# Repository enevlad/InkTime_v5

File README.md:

# InkTime v5

A low-power e-paper smartwatch based on the Nordic nRF52840 SoC, featuring Bluetooth LE, haptic feedback, and a 3-button interface.

## Block Diagram

```
                        ┌─────────────────────────────────────────┐
                        │              nRF52840                    │
                        │                                          │
 USB-C ──► BQ25180 ──►  │  SPI ──► E-Paper Display (2.9")         │
           (LiPo        │  I2C ──► BMA423 (IMU)                   │
           Charger)      │  I2C ──► DRV2605 (Haptic)               │
              │          │  I2C ──► MAX17048 (Fuel Gauge)          │
              ▼          │  I2C ──► BQ25180 (Charger)              │
           RT6160 ──────►│  I2C ──► RT6160 (DC/DC)                 │
           (DC/DC        │  GPIO ► SW_UP, SW_ENT, SW_DN (Buttons)  │
           3.3V)         │  SWD ──► TC2030 Debug Connector         │
                        │  ANT ──► 2450AT18B100E (BLE Antenna)    │
                        └─────────────────────────────────────────┘
```

## Bill of Materials

| Reference | Component | Value | Description | JLC Part | Datasheet |
|-----------|-----------|-------|-------------|----------|-----------|
| U1 | nRF52840 | - | BLE SoC, main MCU | - | - |
| U2 | RT6160AWSC | - | DC/DC Buck Converter 3.3V | - | - |
| U3 | MAX17048G+T10 | - | LiPo Fuel Gauge | - | - |
| U4 | BQ25180YBGR | - | LiPo Charger | - | - |
| U5 | DRV2605YZFR | - | Haptic Driver | - | - |
| U6 | BMA423 | - | IMU (Accelerometer) | - | - |
| U7 | SI1308EDL-T1-GE3 | - | P-Channel MOSFET (EPD Power Switch) | - | - |
| D1 | MBR0530 | - | Schottky Diode (DC/DC) | - | -.pdf) |
| D2, D3 | MBR0530 | - | Schottky Diode (EPD Drive) | - | -.pdf) |
| D4 | USBLC6-2SC6Y | - | USB ESD Protection | - | - |
| L1 | 2450AT18B100E | - | 2.4GHz BLE Chip Antenna | - | - |
| L2 | FTC252012SR47MBCA | 4.7µH | Inductor (DC/DC) | - | - |
| J1 | KH-TYPE-C-16P | - | USB-C Connector | - | - |
| J2 | TC2030-IDC | - | SWD Debug Connector | - | - |
| J3 | 503480-2400 | - | E-Paper FPC Connector 24-pin | - | - |
| SW1 | SW_UP | - | Tactile Button | - | - |
| SW2 | SW_ENT | - | Tactile Button | - | - |
| SW3 | SW_DN | - | Tactile Button | - | - |
| BAT1 | AKYGA LP502030 | 3.7V/250mAh | LiPo Battery | - | - |

## Hardware Description

### Power Architecture

The device is powered by a **3.7V LiPo battery (AKYGA LP502030, 250mAh)**. Charging is handled by the **BQ25180** via USB-C (5V VBUS). The BQ25180 communicates with the nRF52840 over **I²C** (PMC_INT alert pin) for charge status monitoring.

The **RT6160 DC/DC buck converter** steps down VBAT to **3.3V** for the nRF52840 and all peripherals. It is also controlled via I²C from the nRF (SW1/SW2 pins for dynamic voltage scaling).

Battery state of charge is monitored by the **MAX17048 fuel gauge** over I²C (ALERT pin connected to nRF GPIO).

The **E-Paper display** has a separate power rail (**EPD_3V3**) switched by a P-channel MOSFET (SI1308EDL) controlled by a GPIO on the nRF52840. This allows the display to be fully powered off between updates to save energy.

### nRF52840 Pin Assignment

| nRF52840 Pin | Net | Peripheral | Interface |
|-------------|-----|-----------|-----------|
| P0.26 / XL1 | EPD_CLK | E-Paper Display | SPI CLK |
| P0.27 / XL2 | EPD_MOSI | E-Paper Display | SPI MOSI |
| P0.01 | EPD_CS | E-Paper Display | SPI CS |
| P0.00 | EPD_DC | E-Paper Display | SPI DC |
| P0.09 | EPD_RST | E-Paper Display | GPIO |
| P0.10 | EPD_BUSY | E-Paper Display | GPIO Input |
| P0.26 | SCL | I²C Bus (BQ25180, RT6160, MAX17048, DRV2605) | I²C SCL |
| P0.25 | SDA | I²C Bus | I²C SDA |
| P0.06 | IMU_INT1 | BMA423 | GPIO Input |
| P0.05 | IMU_INT2 | BMA423 | GPIO Input |
| P0.07 | HAPTIC_EN | DRV2605 | GPIO Enable |
| P0.08 | EPD_PWR_EN | SI1308EDL Gate | GPIO |
| P0.11 | SW_UP | Button Up | GPIO Input |
| P0.12 | SW_ENT | Button Enter | GPIO Input |
| P0.13 | SW_DN | Button Down | GPIO Input |
| P0.18 | RESET | Reset | Active Low |
| SWDIO | SWDIO | TC2030 SWD | Debug |
| SWDCLK | SWDCLK | TC2030 SWD | Debug |
| ANT | ANT | 2450AT18B100E | RF 2.4GHz |

### E-Paper Display

The E-Paper display connects via a **24-pin FPC connector (503480-2400)**. The drive circuit uses a boost converter based on the SI1308 MOSFET and MBR0530 diodes to generate the high voltages required for the EPD gate drivers (PREVGH ~15V, PREVGL ~-15V). Communication is via SPI.

### IMU

The **BMA423** accelerometer connects via I²C and provides step counting, activity detection, and wrist-tilt detection. Two interrupt lines (IMU_INT1, IMU_INT2) allow wake-on-motion functionality to minimize power consumption.

### Haptic Feedback

The **DRV2605** haptic driver connects via I²C and drives an ERM or LRA vibration motor. It is enabled via a dedicated GPIO from the nRF52840 (HAPTIC_EN).

### BLE Antenna

The **2450AT18B100E** chip antenna is placed at the corner of the PCB with a full copper keepout zone on all layers beneath it, as required by the antenna datasheet for optimal RF performance.

### USB & ESD Protection

The **KH-TYPE-C-16P** USB-C connector includes CC1/CC2 pins for USB PD negotiation. The **USBLC6-2SC6Y** TVS diode array provides ESD protection on the D+/D- lines. A 1kΩ resistor limits inrush current on VBUS.

### SWD Debug Interface

Programming and debugging is done via a **TC2030-IDC Tag-Connect** footprint, exposing SWDIO, SWDCLK, RESET, 3V3, and GND. No physical connector is required — the Tag-Connect pogo-pin cable clips directly onto the PCB pads.

## Power Consumption Estimates

| Mode | Current | Notes |
|------|---------|-------|
| BLE Advertising | ~0.5mA avg | 1s interval |
| BLE Connected | ~1.5mA avg | Active connection |
| Deep Sleep | ~3µA | nRF System OFF, RTC wake |
| E-Paper Refresh | ~20mA peak | During display update only |
| Haptic Active | ~50mA peak | Motor running |
| **Estimated avg (watch mode)** | **~0.3mA** | 1 EPD refresh/min, BLE adv |

Estimated battery life with 250mAh: **~30 days** in watch mode.

## PCB

- **Layers:** 3 (Top signal, GND plane, Bottom signal)
- **Dimensions:** ~54 × 40mm
- **Fabrication:** JLCPCB 4-layer standard
- **Min trace width:** 0.15mm
- **Min clearance:** 0.15mm

## License

Apache License 2.0 — see [LICENSE](LICENSE)

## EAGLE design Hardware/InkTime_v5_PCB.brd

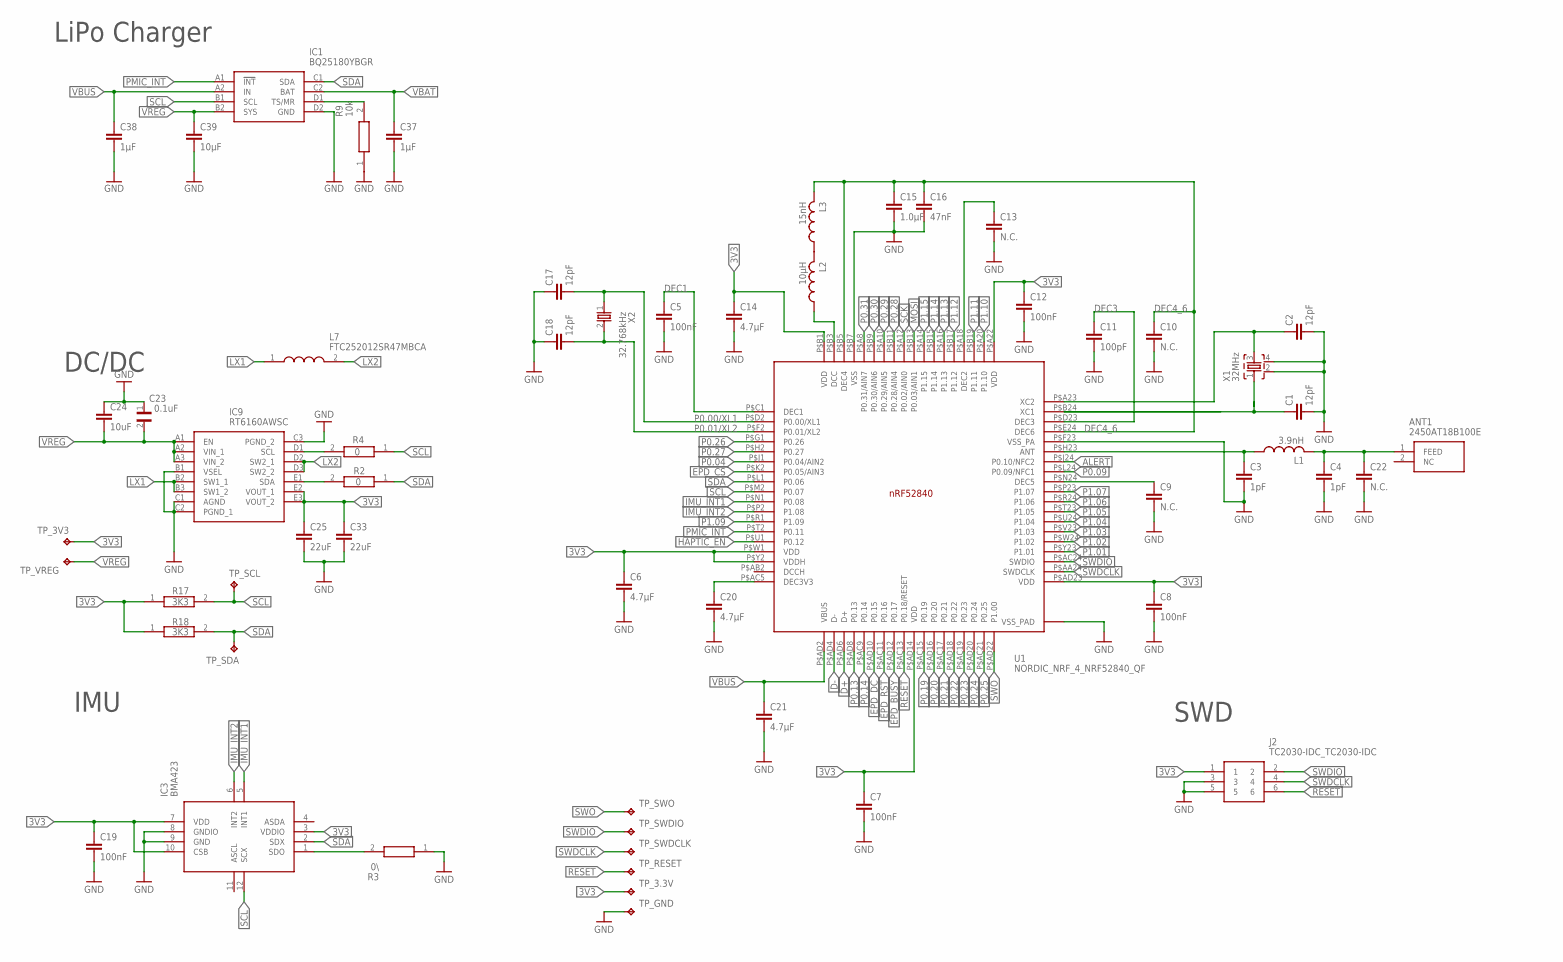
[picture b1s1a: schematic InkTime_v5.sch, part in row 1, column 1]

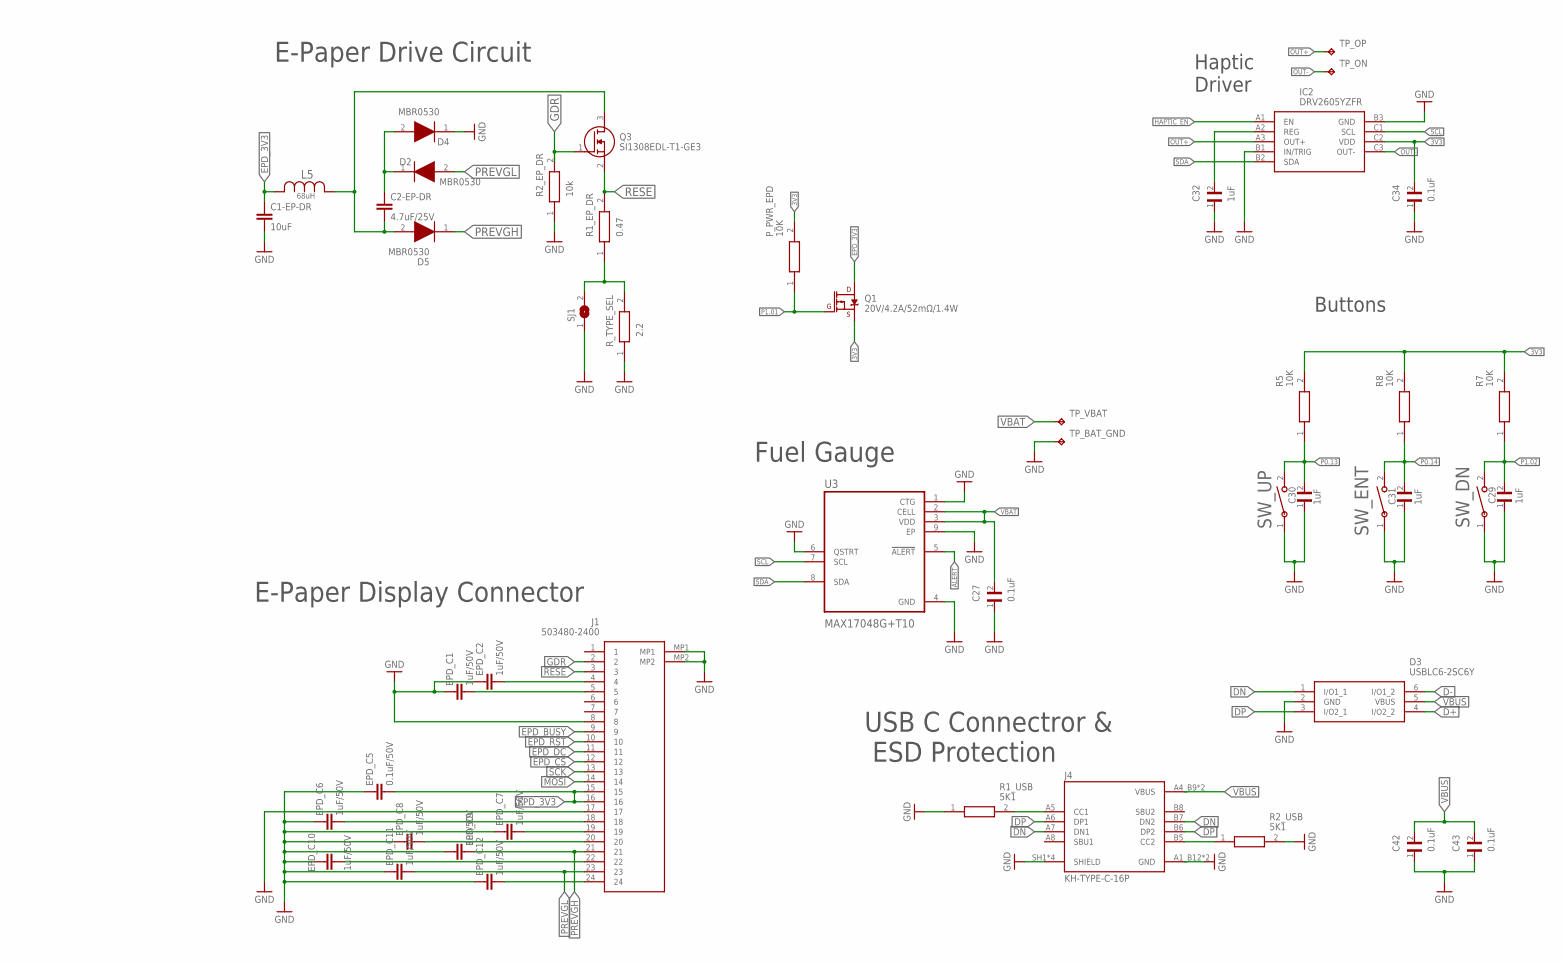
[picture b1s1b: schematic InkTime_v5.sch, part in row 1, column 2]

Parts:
ANT1: 2450AT18B100E; 2450AT18B100E_ANTC3216X140N
C1, C2, C17, C18: 12pF; NORDIC_NRF_3_RESC0201_L
C1-EP-DR, C24: 10uF; PERFECT_0402_0402
C2-EP-DR: 4.7uF/25V; PERFECT_0402_0402
C3, C4: 1pF; NORDIC_NRF_3_RESC0201_L
C5, C7, C8, C12, C19: 100nF; NORDIC_NRF_3_RESC0201_L
C6, C14, C20, C21: 4.7µF; PERFECT_0402_0402
C9, C10, C13, C22: N.C.; NORDIC_NRF_3_RESC0201_L
C11: 100pF; NORDIC_NRF_3_RESC0201_L
C15: 1.0µF; PERFECT_0402_0402
C16: 47nF; NORDIC_NRF_3_RESC0201_L
C23, C27, C34, C42, C43: 0.1uF; GRM011R60J152KE01L_2_CAPC0201X13N
C25, C33: 22uF; PERFECT_0402_0402
C29, C30, C31, C32: 1uF; GRM011R60J152KE01L_2_CAPC0201X13N
C37, C38: 1µF; PERFECT_0402_0402
C39: 10µF; PERFECT_0402_0402
D2, D4, D5: MBR0530; ESP32_C6_LIBRARY_5_SOD3716X135N
D3: USBLC6-2SC6Y; ESP32_C6_LIBRARY_3_SOT95P280X145-6N
EPD_C1, EPD_C2, EPD_C6, EPD_C7, EPD_C8, EPD_C9, EPD_C10, EPD_C11, EPD_C12: 1uF/50V; PERFECT_0402_0402
EPD_C5: 0.1uF/50V; NORDIC_NRF_3_RESC0201_L
IC1: BQ25180YBGR; BQ25180YBGR_BGA8C40P2X4_100X155X50
IC2: DRV2605YZFR; DRV2605YZFR_BGA9C50P3X3_144X144X62
IC3: BMA423; BMA423_BMA423
IC9: RT6160AWSC; RT6160AWSC_BGA15C40P3X5_140X230X60
J1: 503480-2400; 503480-2400_5034802400
J2: TC2030-IDC_TC2030-IDC; TC2030-IDC_TC2030IDC
J4: KH-TYPE-C-16P; KH-TYPE-C-16P_KINGHELM_KH-TYPE-C-16P
L1: 3.9nH; NORDIC_NRF_2_RESC0402_L
L2: 10µH; NORDIC_NRF_2_RESC0402_L
L3: 15nH; NORDIC_NRF_2_RESC0402_L
L5: 68uH; ESP32_C6_LIBRARY_2_IND_4828-WE-TPC_WRE
L7: FTC252012SR47MBCA; MLP2016SR47MT0S1_INDC2016X100N
P_PWR_EPD: 10K; ERA-1AEB3401C_0201
Q1: 20V/4.2A/52mΩ/1.4W; ESP32_C6_LIBRARY_4_ESP32_C6_LIBRARY_4_ESP32_C6_LIBRARY_4_ES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
Q3: SI1308EDL-T1-GE3; ESP32_C6_LIBRARY_6_SOT65P210X110-3N
R1_EP_DR: 0.47; CPF0201D7K68C1_0201
R1_USB, R2_USB: 5K1; ERA-1AEB3401C_0201
R2: 0; ERA-1AEB3401C_0201
R2_EP_DR, R9: 10k; CPF0201D7K68C1_0201
R3: 0\; CPF0201D7K68C1_0201
R4: 0; CPF0201D7K68C1_0201
R5, R7, R8: 10K; ERA-1AEB3401C_0201
R17, R18: 3K3; ERA-1AEB3401C_0201
R_TYPE_SEL: 2.2; CPF0201D7K68C1_0201
SJ1: ESP32_C6_LIBRARY_7_JUMPER_SJ
SW_DN: 2025-10-22_07-23-44_LIBRARY_EVP-AKE31ASW_EVP-AKE3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; 2025-10-22_07-23-44_LIBRARY_SW_EVP-AKE31A_PAN
SW_ENT: 2025-10-22_07-23-44_LIBRARY_EVP-AKE31ASW_EVP-AKE3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; 2025-10-22_07-23-44_LIBRARY_SW_EVP-AKE31A_PAN
SW_UP: 2025-10-22_07-23-44_LIBRARY_EVP-AKE31ASW_EVP-AKE3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; 2025-10-22_07-23-44_LIBRARY_SW_EVP-AKE31A_PAN
TP_3.3V, TP_3V3: HECTOR_WATCH_1_TPTP20R; HECTOR_WATCH_1_TP20R
TP_BAT_GND: HECTOR_WATCH_1_TPTP20R; HECTOR_WATCH_1_TP20R
TP_GND: HECTOR_WATCH_1_TPTP20R; HECTOR_WATCH_1_TP20R
TP_ON: HECTOR_WATCH_1_TPTP20R; HECTOR_WATCH_1_TP20R
TP_OP: HECTOR_WATCH_1_TPTP20R; HECTOR_WATCH_1_TP20R
TP_RESET: HECTOR_WATCH_1_TPTP20R; HECTOR_WATCH_1_TP20R
TP_SCL: HECTOR_WATCH_1_TPTP20R; HECTOR_WATCH_1_TP20R
TP_SDA: HECTOR_WATCH_1_TPTP20R; HECTOR_WATCH_1_TP20R
TP_SWDCLK: HECTOR_WATCH_1_TPTP20R; HECTOR_WATCH_1_TP20R
TP_SWDIO: HECTOR_WATCH_1_TPTP20R; HECTOR_WATCH_1_TP20R
TP_SWO: HECTOR_WATCH_1_TPTP20R; HECTOR_WATCH_1_TP20R
TP_VBAT: HECTOR_WATCH_1_TPTP20R; HECTOR_WATCH_1_TP20R
TP_VREG: HECTOR_WATCH_1_TPTP20R; HECTOR_WATCH_1_TP20R
U1: NORDIC_NRF_4_NRF52840_QF; NORDIC_NRF_4_AQFN50P700X700X85_HS-74N
U3: MAX17048G+T10; ESP32_C6_LIBRARY_SON50P200X200X80-9N
X1: 32MHz; NORDIC_NRF_BT-XTAL_2016_N
X2: 32.768kHz; NORDIC_NRF_1_XTAL_3215_N

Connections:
3V3: C6.1, C7.1, C8.1, C12.1, C14.1, C19.1, C25.1, C33.1, C34.2, IC2.C2 (VDD), IC3.3 (VDDIO), IC3.7 (VDD), IC3.10 (CSB), IC9.E2 (VOUT_1), IC9.E3 (VOUT_2), J2.1, P_PWR_EPD.2, Q1.2 (S), R5.2, R7.2, R8.2, R17.1, R18.1, TP_3.3V.TP, TP_3V3.TP, U1.P$A22 (VDD), U1.P$AD14 (VDD), U1.P$AD23 (VDD), U1.P$B1 (VDD), U1.P$W1 (VDD), U1.P$Y2 (VDDH)
ALERT: U1.P$J24 (P0.10/NFC2), U3.5 (!ALERT)
D+: D3.4 (I/O2_2), U1.P$AD6 (D+)
D-: D3.6 (I/O1_2), U1.P$AD4 (D-)
DEC1: C5.1, U1.P$C1 (DEC1)
DEC3: C11.1, U1.P$D23 (DEC3)
DEC4_6: C10.1, C15.1, C16.1, L3.2, U1.P$B5 (DEC4), U1.P$E24 (DEC6)
DN: D3.1 (I/O1_1), J4.A7 (DN1), J4.B7 (DN2)
DP: D3.3 (I/O2_1), J4.A6 (DP1), J4.B6 (DP2)
EPD_3V3: C1-EP-DR.1, EPD_C5.2, J1.15, J1.16, L5.2, Q1.3 (D)
EPD_BUSY: J1.9, U1.P$AD12 (P0.17)
EPD_CS: J1.12, U1.P$K2 (P0.05/AIN3)
EPD_DC: J1.11, U1.P$AD10 (P0.15)
EPD_RST: J1.10, U1.P$AC11 (P0.16)
GDR: J1.2, Q3.1 (G), R2_EP_DR.2
GND: C1.2, C1-EP-DR.2, C2.2, C3.2, C4.2, C5.2, C6.2, C7.2, C8.2, C9.2, C10.2, C11.2, C12.2, C13.2, C14.2, C15.2, C16.2, C17.1, C18.1, C19.2, C20.2, C21.2, C22.2, C23.1, C24.1, C25.2, C27.1, C29.1, C30.1, C31.1, C32.1, C33.2, C34.1, C37.2, C38.2, C39.2, C42.1, C43.1, D3.2 (GND), D4.1 (K), EPD_C1.1, EPD_C2.1, EPD_C5.1, EPD_C6.1, EPD_C7.1, EPD_C8.1, EPD_C9.1, EPD_C10.1, EPD_C11.1, EPD_C12.1, IC1.D2 (GND), IC2.B1 (IN/TRIG), IC2.B3 (GND), IC3.8 (GNDIO), IC3.9 (GND), IC9.B1 (VSEL), IC9.C1 (AGND), IC9.C2 (PGND_1), IC9.C3 (PGND_2), J1.8, J1.17, J1.MP1, J1.MP2, J2.3, J2.5, J4.A1_B12 (GND), J4.A12_B1 (GND), J4.SH1 (SHIELD), J4.SH2 (SHIELD), J4.SH3 (SHIELD), J4.SH4 (SHIELD), R1_USB.1, R2_EP_DR.1, R2_USB.2, R3.1, R9.1, SJ1.1, SW_DN.1, SW_ENT.1, SW_UP.1, TP_BAT_GND.TP, TP_GND.TP, U1.P$74 (VSS_PAD), U1.P$75 (VSS_PAD), U1.P$76 (VSS_PAD), U1.P$77 (VSS_PAD), U1.P$78 (VSS_PAD), U1.P$79 (VSS_PAD), U1.P$80 (VSS_PAD), U1.P$81 (VSS_PAD), U1.P$82 (VSS_PAD), U1.P$83 (VSS_PAD), U1.P$84 (VSS_PAD), U1.P$85 (VSS_PAD), U1.P$86 (VSS_PAD), U1.P$87 (VSS_PAD), U1.P$88 (VSS_PAD), U1.P$89 (VSS_PAD), U1.P$90 (VSS_PAD), U1.P$B7 (VSS), U1.P$F23 (VSS_PA), U3.1 (CTG), U3.4 (GND), U3.6 (QSTRT), U3.9 (EP), X1.2, X1.4
HAPTIC_EN: IC2.A1 (EN), U1.P$U1 (P0.12)
IMU_INT1: IC3.5 (INT1), U1.P$N1 (P0.08)
IMU_INT2: IC3.6 (INT2), U1.P$P2 (P1.08)
LX1: IC9.B2 (SW1_1), IC9.B3 (SW1_2), L7.1
LX2: IC9.D2 (SW2_1), IC9.D3 (SW2_2), L7.2
MOSI: J1.14, U1.P$B13 (P0.03/AIN1)
unnamed: IC1.D1 (TS/MR), R9.2
unnamed: IC9.D1 (SCL), R4.2
unnamed: IC9.E1 (SDA), R2.2
unnamed: IC3.1 (SDO), R3.2
unnamed: C20.1, U1.P$AC5 (DEC3V3)
unnamed: L2.1, U1.P$B3 (DCC)
unnamed: L2.2, L3.1
unnamed: C2.1, U1.P$A23 (XC2), X1.3
unnamed: C13.1, U1.P$A18 (DEC2)
unnamed: C1.1, U1.P$B24 (XC1)
unnamed: ANT1.1 (FEED), C4.1, C22.1, L1.2
unnamed: C3.1, L1.1, U1.P$H23 (ANT)
unnamed: C9.1, U1.P$N24 (DEC5)
unnamed: C32.2, IC2.A2 (REG)
unnamed: C2-EP-DR.2, D5.2 (A), L5.1, Q3.3 (D)
unnamed: C2-EP-DR.1, D2.1 (K), D4.2 (A)
unnamed: R1_EP_DR.1, R_TYPE_SEL.2, SJ1.2
unnamed: EPD_C2.2, J1.4
unnamed: EPD_C1.2, J1.5
unnamed: EPD_C6.2, J1.18
unnamed: EPD_C7.2, J1.19
unnamed: EPD_C8.2, J1.20
unnamed: J4.A5 (CC1), R1_USB.2
unnamed: EPD_C10.2, J1.22
unnamed: J4.B5 (CC2), R2_USB.1
unnamed: EPD_C12.2, J1.24
OUT+: IC2.A3 (OUT+), TP_OP.TP
OUT-: IC2.C3 (OUT-), TP_ON.TP
P0.00/XL1: C17.2, U1.P$D2 (P0.00/XL1), X2.1
P0.01/XL2: C18.2, U1.P$F2 (P0.01/XL2), X2.2
P0.04: U1.P$J1 (P0.04/AIN2)
P0.09: U1.P$L24 (P0.09/NFC1)
P0.13: C30.2, R5.1, SW_UP.2, U1.P$AD8 (P0.13)
P0.14: C31.2, R8.1, SW_ENT.2, U1.P$AC9 (P0.14)
P0.19: U1.P$AC15 (P0.19)
P0.20: U1.P$AD16 (P0.20)
P0.21: U1.P$AC17 (P0.21)
P0.22: U1.P$AD18 (P0.22)
P0.23: U1.P$AC19 (P0.23)
P0.24: U1.P$AD20 (P0.24)
P0.25: U1.P$AC21 (P0.25)
P0.26: U1.P$G1 (P0.26)
P0.27: U1.P$H2 (P0.27)
P0.28: U1.P$B11 (P0.28/AIN4)
P0.29: U1.P$A10 (P0.29/AIN5)
P0.30: U1.P$B9 (P0.30/AIN6)
P0.31: U1.P$A8 (P0.31/AIN7)
P1.01: P_PWR_EPD.1, Q1.1 (G), U1.P$Y23 (P1.01)
P1.02: C29.2, R7.1, SW_DN.2, U1.P$W24 (P1.02)
P1.03: U1.P$V23 (P1.03)
P1.04: U1.P$U24 (P1.04)
P1.05: U1.P$T23 (P1.05)
P1.06: U1.P$R24 (P1.06)
P1.07: U1.P$P23 (P1.07)
P1.09: U1.P$R1 (P1.09)
P1.10: U1.P$A20 (P1.10)
P1.11: U1.P$B19 (P1.11)
P1.12: U1.P$B17 (P1.12)
P1.13: U1.P$A16 (P1.13)
P1.14: U1.P$B15 (P1.14)
P1.15: U1.P$A14 (P1.15)
PMIC_INT: IC1.A1 (!INT), U1.P$T2 (P0.11)
PREVGH: D5.1 (K), EPD_C9.2, J1.21
PREVGL: D2.2 (A), EPD_C11.2, J1.23
RESE: J1.3, Q3.2 (S), R1_EP_DR.2
RESET: J2.6, TP_RESET.TP, U1.P$AC13 (P0.18/RESET)
SCK: J1.13, U1.P$A12 (P0.02/AIN0)
SCL: IC1.B1 (SCL), IC2.C1 (SCL), IC3.12 (SCX), R4.1, R17.2, TP_SCL.TP, U1.P$M2 (P0.07), U3.7 (SCL)
SDA: IC1.C1 (SDA), IC2.B2 (SDA), IC3.2 (SDX), R2.1, R18.2, TP_SDA.TP, U1.P$L1 (P0.06), U3.8 (SDA)
SWDCLK: J2.4, TP_SWDCLK.TP, U1.P$AA24 (SWDCLK)
SWDIO: J2.2, TP_SWDIO.TP, U1.P$AC24 (SWDIO)
SWO: TP_SWO.TP, U1.P$AD22 (P1.00)
VBAT: C27.2, C37.1, IC1.C2 (BAT), TP_VBAT.TP, U3.2 (CELL), U3.3 (VDD)
VBUS: C21.1, C38.1, C42.2, C43.2, D3.5 (VBUS), IC1.A2 (IN), J4.A4_B9 (VBUS), J4.A9_B4 (VBUS), U1.P$AD2 (VBUS)
VREG: C23.2, C24.2, C39.1, IC1.B2 (SYS), IC9.A1 (EN), IC9.A2 (VIN_1), IC9.A3 (VIN_2), TP_VREG.TP

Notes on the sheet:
LiPo Charger
DC/DC
IMU
SWD
E-Paper Drive Circuit
E-Paper Display Connector
Fuel Gauge
Haptic Driver
Buttons
USB C Connectror & ESD Protection

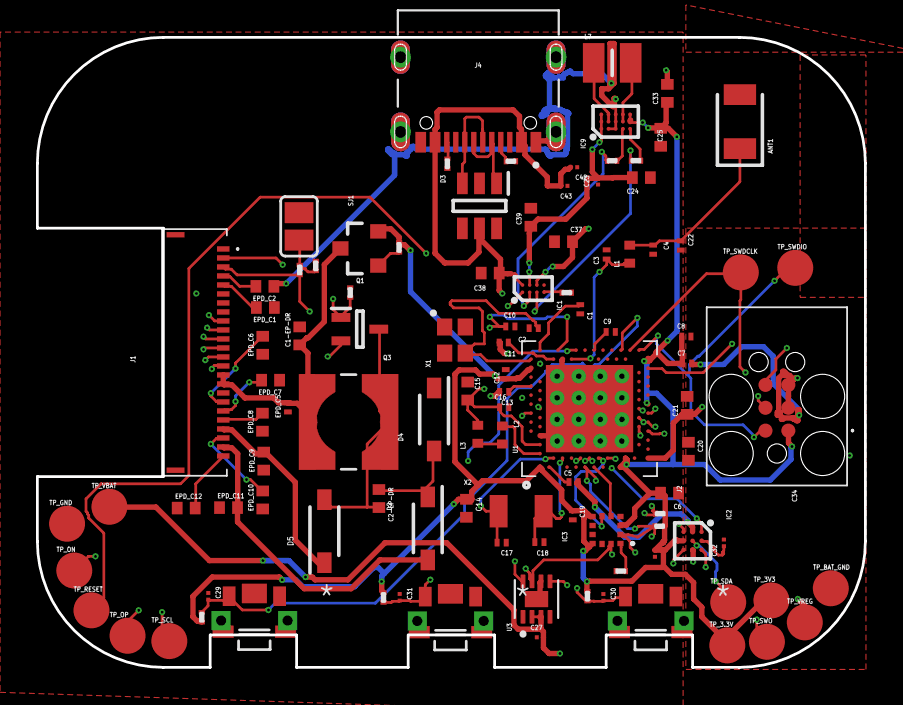
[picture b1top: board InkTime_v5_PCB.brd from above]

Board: 4 copper layers, 46.0 x 35.0 mm, 105 parts (0 on the bottom side), 70 nets.

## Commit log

2026-04-10 Enhance README with hardware details and diagrams
    Added detailed hardware description, block diagram, and bill of materials for InkTime v5 smartwatch.
2026-04-19 Update LICENSE

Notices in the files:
parts and their libraries:
InkTime_v5: COPYRIGHT: Copyright (C) 2024 Ultra Librarian. All rights reserved.
InkTime_v5: COPYRIGHT: Copyright (C) 2025 Ultra Librarian. All rights reserved.
